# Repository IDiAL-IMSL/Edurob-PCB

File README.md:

# Edurob-PCB
PCB-Files for Edurob

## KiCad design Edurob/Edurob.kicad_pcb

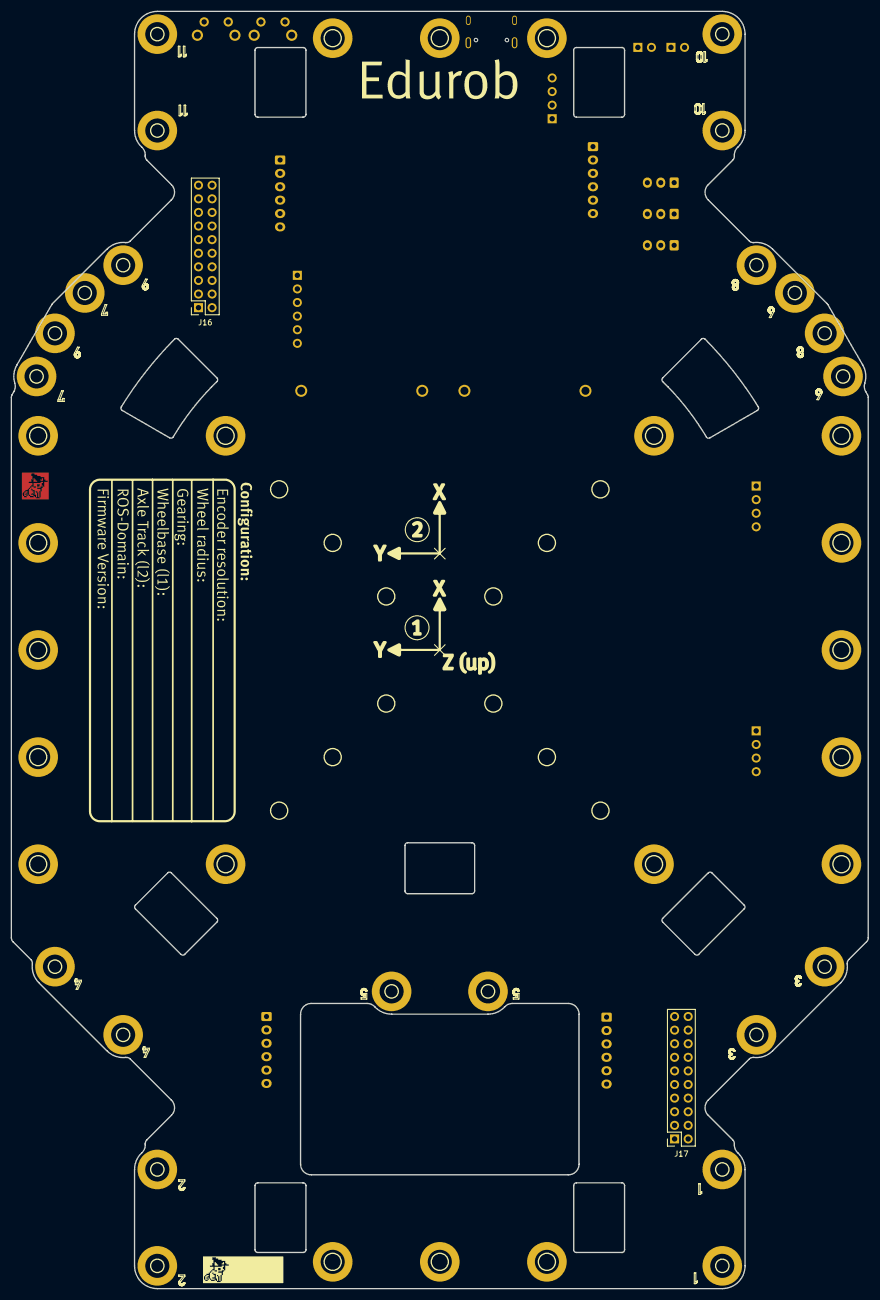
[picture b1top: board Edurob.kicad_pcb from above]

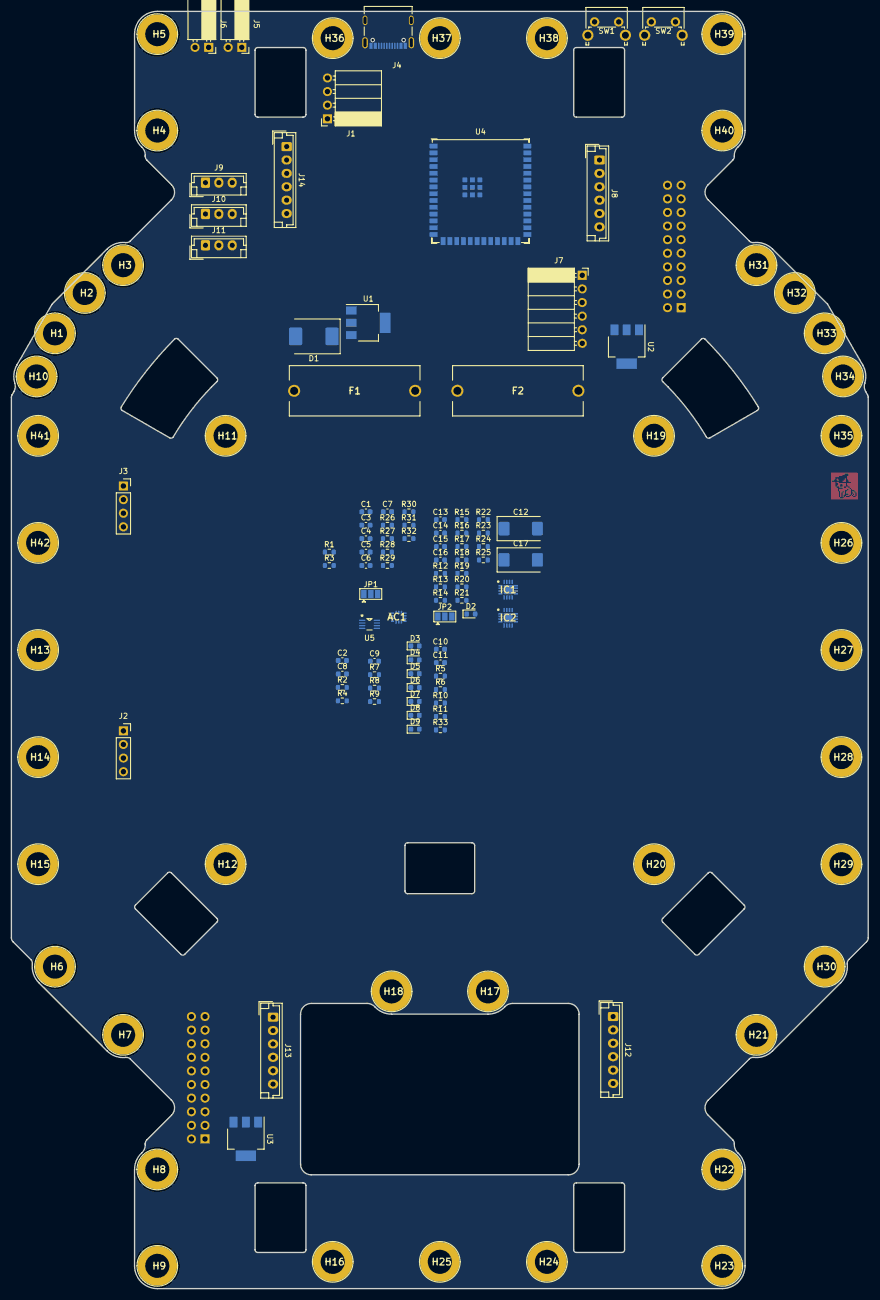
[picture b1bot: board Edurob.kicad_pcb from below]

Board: 2 copper layers, 160.0 x 238.5 mm, 133 parts (129 on the bottom side), 70 nets, no tracks yet.

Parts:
AC1: LSM6DSOXTR; LGA-14_1
C1, C3, C6: 10uF; C_0603_1608Metric
C2, C8: 1uF; C_0603_1608Metric
C4, C5, C7: 22uF; C_0603_1608Metric
C9, C10, C11, C13, C14, C15, C16: 100nF; C_0603_1608Metric
C12, C17: 47uF; CP_EIA-7343-31_Kemet-D
D1: B320; D_SMC
D2, D3, D4, D5, D6, D7, D8, D9: LED; LED_0603_1608Metric
F1, F2: 0PTF0078P
H1, H2, H3, H4, H5, H6, H7, H8, H9, H10, H11, H12, H13, H14, H15, H16, H17, H18, H19, H20, H21, H22, H23, H24, H25, H26, H27, H28, H29, H30, H31, H32, H33, H34, H35, H36, H37, H38, H39, H40, H41, H42: 9775026360R
IC1, IC2: TC78H660FTG,EL; QFN50P300X300X90-17N
J1: OLED; PinSocket_1x04_P2.54mm_Horizontal
J2, J3: Conn_01x04_Pin; PinSocket_1x04_P2.54mm_Vertical
J4: 12402012E212A; AMPHENOL_12402012E212A
J5, J6: Conn_01x02_Pin; PinSocket_1x02_P2.54mm_Horizontal
J7: Conn_01x06_Pin; PinSocket_1x06_P2.54mm_Horizontal
J8, J12, J13, J14: Conn_01x06_Pin; JST_EH_B6B-EH-A_1x06_P2.50mm_Vertical
J9, J10, J11: Conn_01x03_Male; JST_EH_B3B-EH-A_1x03_P2.50mm_Vertical
J16, J17: Conn_01x20_Pin; PinSocket_2x10_P2.54mm_Vertical
JP1, JP2: SolderJumper_3_Open; SolderJumper-3_P1.3mm_Open_Pad1.0x1.5mm
LOGO1: Logo; Logo_Cat_Copper_5x5
LOGO2: Logo; Logo_Cat_15x5
R1, R3: 5k1; R_0603_1608Metric
R2, R4, R5, R6, R10, R11, R14, R15, R16, R17, R18, R20, R21, R22, R23, R24, R33: 10k; R_0603_1608Metric
R7, R8, R9, R12: 10K; R_0603_1608Metric
R13, R19: 47K; R_0603_1608Metric
R25, R30, R31, R32: 130R; R_0603_1608Metric
R26, R27, R28, R29: 300R; R_0603_1608Metric
SW1, SW2: SW_Push; SW_Tactile_SPST_Angled_PTS645Vx83-2LFS
U1, U2, U3: AZ1117-3.3; SOT-223-3_TabPin2
U4: ESP32-S3-WROOM-1; ESP32-S3-WROOM-1U
U5: 74LVC2G241DCUTG4

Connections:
DXL_DATA: J9.3, J10.3, J11.3, R9.2, U5.2 (1A), U5.3 (2Y)
DXL_RXD: J16.10, J17.10, R8.2, U4.9 (GPIO16/U0CTS/ADC2_CH5/XTAL_32K_N), U5.6 (1Y)
DXL_TXD: J16.9, J17.9, U4.8 (GPIO15/U0RTS/ADC2_CH4/XTAL_32K_P), U5.5 (2A)
DXL_TXEN: J16.11, J17.11, R7.1, U4.15 (GPIO3/TOUCH3/ADC1_CH2), U5.1 (*1OE), U5.7 (2OE)
EspBoot: C8.1, J6.1, J7.5, R4.2, SW1.1, U4.27 (GPIO0/BOOT)
EspEn: C2.1, J5.1, J7.4, R2.2, SW2.1, U4.3 (EN)
GND: AC1.2 (SDX), AC1.3 (SCX), AC1.6 (GND_1), AC1.7 (GND_2), C1.2, C2.2, C3.2, C4.2, C5.2, C6.2, C7.2, C8.2, C9.2, C10.2, C11.2, C12.2, C13.2, C14.2, C15.2, C16.2, C17.2, D2.1 (K), D3.1 (K), D4.1 (K), D5.1 (K), D6.1 (K), D7.1 (K), D8.1 (K), D9.1 (K), H1.1, H2.1, H3.1, H4.1, H5.1, H6.1, H7.1, H8.1, H9.1, H10.1, H11.1, H12.1, H13.1, H14.1, H15.1, H16.1, H17.1, H18.1, H19.1, H20.1, H21.1, H22.1, H23.1, H24.1, H25.1, H26.1, H27.1, H28.1, H29.1, H30.1, H31.1, H32.1, H33.1, H34.1, H35.1, H36.1, H37.1, H38.1, H39.1, H40.1, H41.1, H42.1, IC1.2 (AGND), IC1.4 (PGND_A), IC1.9 (PGND_B), IC1.17 (EP), IC2.2 (AGND), IC2.4 (PGND_A), IC2.9 (PGND_B), IC2.17 (EP), J1.4, J2.4, J3.4, J4.A1_B12 (GND), J4.B1_A12 (GND__1), J5.2, J6.2, J7.6, J8.2, J9.1, J10.1, J11.1, J12.2, J13.2, J14.2, J16.1, J16.2, J17.1, J17.2, R1.1, R3.2, R5.2, R7.2, R11.2, R12.2, R13.2, R15.2, R19.2, R33.2, SW1.2, SW2.2, U1.1 (GND), U2.1 (GND), U3.1 (GND), U4.1 (GND), U4.40 (GND), U4.41 (GND), U5.4 (GND)
I2C_SCL: J16.13, J17.13, U4.17 (GPIO9/TOUCH9/ADC1_CH8/FSPIHD/SUBSPIHD)
I2C_SDA: J16.12, J17.12, U4.12 (GPIO8/TOUCH8/ADC1_CH7/SUBSPICS1)
IMU_INT1: AC1.4 (INT1), J16.18, J17.18, R11.1, U4.26 (GPIO45)
IMU_INT2: AC1.9 (INT2), J16.19, J17.19, R33.1, U4.16 (GPIO46)
MOT_A_DIR: IC1.1 (IN1A_/_PHASE_A), U4.11 (GPIO18/U1RXD/ADC2_CH7/CLK_OUT3)
MOT_A_ENCA: J8.4, R16.2, U4.38 (GPIO2/TOUCH2/ADC1_CH1)
MOT_A_ENCB: J8.3, R17.2, U4.39 (GPIO1/TOUCH1/ADC1_CH0)
MOT_A_PWM: IC1.15 (IN1B_/_ENABLE_A), U4.32 (MTCK/GPIO39/CLK_OUT3/SUBSPICS1)
MOT_B_DIR: IC1.14 (IN2A_/_PHASE_B), U4.23 (GPIO21)
MOT_B_ENCA: J12.4, R18.2, U4.5 (GPIO5/TOUCH5/ADC1_CH4)
MOT_B_ENCB: J12.3, R20.2, U4.4 (GPIO4/TOUCH4/ADC1_CH3)
MOT_B_PWM: IC1.16 (IN2B_/_ENABLE_B), U4.35 (MTMS/GPIO42)
MOT_C_DIR: IC2.1 (IN1A_/_PHASE_A), U4.31 (GPIO38/FSPIWP/SUBSPIWP)
MOT_C_ENCA: J13.4, R21.2, U4.7 (GPIO7/TOUCH7/ADC1_CH6)
MOT_C_ENCB: J13.3, R22.2, U4.6 (GPIO6/TOUCH6/ADC1_CH5)
MOT_C_PWM: IC2.15 (IN1B_/_ENABLE_A), U4.34 (MTDI/GPIO41/CLK_OUT1)
MOT_D_DIR: IC2.14 (IN2A_/_PHASE_B), U4.24 (GPIO47/SPICLK_P/SUBSPICLK_P_DIFF)
MOT_D_ENCA: J14.4, R23.2, U4.10 (GPIO17/U1TXD/ADC2_CH6)
MOT_D_ENCB: J14.3, R24.2, U4.22 (GPIO14/TOUCH14/ADC2_CH3/FSPIWP/FSPIDQS/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)
MOT_D_PWM: IC2.16 (IN2B_/_ENABLE_B), U4.33 (MTDO/GPIO40/CLK_OUT2)
MOT_OA+: IC1.5 (OUT_A+), J8.1
MOT_OA-: IC1.6 (OUT_A-), J8.6
MOT_OB+: IC1.8 (OUT_B+), J12.1
MOT_OB-: IC1.7 (OUT_B-), J12.6
MOT_OC+: IC2.5 (OUT_A+), J13.1
MOT_OC-: IC2.6 (OUT_A-), J13.6
MOT_OD+: IC2.8 (OUT_B+), J14.1
MOT_OD-: IC2.7 (OUT_B-), J14.6
MOT_STBY: IC1.12 (STBY), IC2.12 (STBY), J16.20, J17.20, R12.1, R25.1, U4.25 (GPIO48/SPICLK_N/SUBSPICLK_N_DIFF)
unnamed: AC1.12 (CS), R10.2
unnamed: AC1.1 (SDO/SA0), JP1.2 (C)
unnamed: D2.2 (A), R25.2
unnamed: D3.2 (A), R26.2
unnamed: D4.2 (A), R27.2
unnamed: D5.2 (A), R28.2
unnamed: D6.2 (A), R29.2
unnamed: D7.2 (A), R30.2
unnamed: D8.2 (A), R31.2
unnamed: D9.2 (A), R32.2
unnamed: IC1.13 (MODE_/_ERR), IC2.13 (MODE_/_ERR), JP2.2 (C)
unnamed: IC1.11 (OSCM), R13.1
unnamed: IC2.11 (OSCM), R19.1
unnamed: J4.A5 (CC1_A), R1.2
unnamed: J4.B5 (CC1_B), R3.1
unnamed: JP1.1 (A), R5.1
unnamed: JP1.3 (B), R6.2
unnamed: JP2.1 (A), R14.2
unnamed: JP2.3 (B), R15.1
SPI_CS0: J16.14, J17.14, U4.18 (GPIO10/TOUCH10/ADC1_CH9/FSPICS0/FSPIIO4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)
SPI_MISO: J16.17, J17.17, U4.21 (GPIO13/TOUCH13/ADC2_CH2/FSPIQ/FSPIIO7/S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)
SPI_MOSI: J16.15, J17.15, U4.19 (GPIO11/TOUCH11/ADC2_CH0/FSPID/FSPIIO5/S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)
SPI_SCK: J16.16, J17.16, U4.20 (GPIO12/TOUCH12/ADC2_CH1/FSPICLK/FSPIIO6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)
UART0_RXD: J7.3, J16.8, J17.8, U4.36 (U0RXD/GPIO44/CLK_OUT2)
UART0_TXD: J7.2, J16.7, J17.7, U4.37 (U0TXD/GPIO43/CLK_OUT1)
USB_D+: J4.A6 (D+_A), J4.B6 (D+_B), U4.14 (GPIO20/U1CTS/ADC2_CH9/CLK_OUT1/USB_D+)
USB_D-: J4.A7 (D-_A), J4.B7 (D-_B), U4.13 (GPIO19/U1RTS/ADC2_CH8/CLK_OUT2/USB_D-)
VBATT: F1.1, F2.1, J2.1, J3.1, R26.1
VLOG+3V3: AC1.5 (VDDIO), AC1.8 (VDD), C4.1, C9.1, C10.1, C11.1, C14.1, C15.1, J1.3, J7.1, J8.5, J12.5, J13.5, J14.5, R2.1, R4.1, R6.1, R8.1, R9.1, R10.1, R14.1, R16.1, R17.1, R18.1, R20.1, R21.1, R22.1, R23.1, R24.1, R30.1, U1.2 (VO), U4.2 (3V3), U5.8 (VCC)
VLOG+5V: C1.1, C3.1, C6.1, D1.1 (K), F1.2, J9.2, J10.2, J11.2, J16.3, J16.4, J17.3, J17.4, R27.1, U1.3 (VI), U2.3 (VI), U3.3 (VI)
VMOT+5V: C12.1, C13.1, C16.1, C17.1, F2.2, IC1.3 (VM), IC2.3 (VM), R29.1
VSENS1+3V3: C5.1, J16.5, J16.6, R31.1, U2.2 (VO)
VSENS2+3V3: C7.1, J17.5, J17.6, R32.1, U3.2 (VO)
VUSB: D1.2 (A), J4.A4_B9 (VBUS), J4.B4_A9 (VBUS__1), R28.1

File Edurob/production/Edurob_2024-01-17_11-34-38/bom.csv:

Designator,Footprint,Quantity,Value,LCSC Part #
AC1,LGA-14_1,1,LSM6DSOXTR,
"C1, C3, C6",0603,3,10uF,
"C10, C11, C13, C14, C15, C16, C9",0603,7,100nF,
"C12, C17",CP_EIA-7343-31_Kemet-D,2,47uF,
"C2, C8",0603,2,1uF,
"C4, C5, C7",0603,3,22uF,
D1,D_SMC,1,B320,
"D2, D3, D4, D5, D6, D7, D8, D9",0603,8,LED,
"F1, F2",0PTF0078P,2,0PTF0078P,
"H1, H10, H11, H12, H15, H16, H17, H18, H19, H2, H20, H21, H22, H23, H24, H29, H3, H30, H31, H32, H33, H34, H35, H36, H38, H39, H4, H40, H41, H5, H6, H7, H8, H9",9775026360R,34,9775026360R,
"IC1, IC2",QFN50P300X300X90-17N,2,"TC78H660FTG,EL",
IC3,QFN50P400X400X90-25N,1,PI4IOE5V6416ZDEX,
J1,PinSocket_1x04_P2.54mm_Horizontal,1,OLED,
"J10, J9",JST_EH_B3B-EH-A_1x03_P2.50mm_Vertical,2,Conn_01x03_Male,
"J11, J2, J3, J6",PinSocket_1x04_P2.54mm_Vertical,4,Conn_01x04_Pin,
"J12, J13, J14, J8",JST_EH_B6B-EH-A_1x06_P2.50mm_Vertical,4,Conn_01x06_Pin,
"J15, J16, J17, J18",PinSocket_2x10_P2.54mm_Vertical,4,Conn_01x20_Pin,
J4,AMPHENOL_12402012E212A,1,12402012E212A,
J5,PinSocket_1x04_P2.54mm_Horizontal,1,Conn_01x04_Pin,
J7,PinSocket_1x06_P2.54mm_Horizontal,1,Conn_01x06_Pin,
"JP1, JP2, JP3",SolderJumper-3_P1.3mm_Open_Pad1.0x1.5mm,3,SolderJumper_3_Open,
LOGO1,Logo_Cat_Copper_5x5,1,Logo,
LOGO2,Logo_Cat_15x5,1,Logo,
"R1, R3",0603,2,5k1,
"R10, R11, R12, R14, R15, R16, R17, R18, R2, R20, R21, R22, R23, R24, R33, R34, R35, R36, R37, R4, R5, R6, R7, R8, R9",0603,25,10k,
"R13, R19",0603,2,47K,
"R25, R30, R31, R32",0603,4,130R,
"R26, R27, R28, R29",0603,4,300R,
"SW1, SW2",SW_Tactile_SPST_Angled_PTS645Vx83-2LFS,2,SW_Push,
"U1, U2, U3",SOT-223-3_TabPin2,3,AZ1117-3.3,
U4,ESP32-S3-WROOM-1U,1,ESP32-S3-WROOM-1,
U5,74LVC2G241DCUTG4,1,74LVC2G241DCUTG4,

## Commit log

2024-01-03 Initial upload
2024-01-05 Added GPIO Expander, finalized Connector positions
2024-01-05 Finalized part placement
2024-01-19 Finished routing and part placement
2024-01-19 Finished silkscreen + fixed board outline
2024-05-27 Release v1.0.1
2024-05-27 pcb img test
2025-03-25 Update
    Updated Images, Small adjustments
2025-03-25 Fixed image path
2025-05-25 Added all Parts and Reference drawings
2025-05-25 Revert "Added all Parts and Reference drawings"
    This reverts commit 141b38322698b7adff6639faecd635cc100a06d4.
